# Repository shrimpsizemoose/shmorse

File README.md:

# Morse Code ATtiny85

Поупражняться с attiny85, светодиодами и пищалкой. В целом можно делать что угодно, но вообще идея что это что-то типа азбуки морзе, а кнопка это переключатель между состояниями.

Схема сделана в KiCad, вот отличный туториал который я использовал чтобы разобраться, как это делается: https://www.youtube.com/watch?v=vLnu21fS22s&list=PLUOaI24LpvQPls1Ru_qECJrENwzD7XImd

## Schematic

Собственно, схема. Никаких выключателей, только хардкор, только писк

## PCB Layout

Всё залито землёй, поэтому ножки которые идут на землю никуда не идут, _удобно!_

## Build Examples

Один из резисторов стоит неудобно, но в целом выкрутиться можно если не присоединять слот под батарейку.

## Компоненты
* Микроконтроллер ATtiny85-20P (ATtiny45 тоже подойдёт)
* 8-pin панелька под микросхему (можно без неё если не планируешь вынимать микроконтроллер)
* 3x 1kΩ резистора
* 3x 5mm светодиодов
* 1x 6x6mm кнопка
* 1x пищалка 12mm (растояние между ножек 7.5мм)
* 1x разъём под батарейку CR2032 -- :warning: в v1.0 нестандартное расстояние между ножек 20.5mm, возможно проще без него проводки к контактам припаять

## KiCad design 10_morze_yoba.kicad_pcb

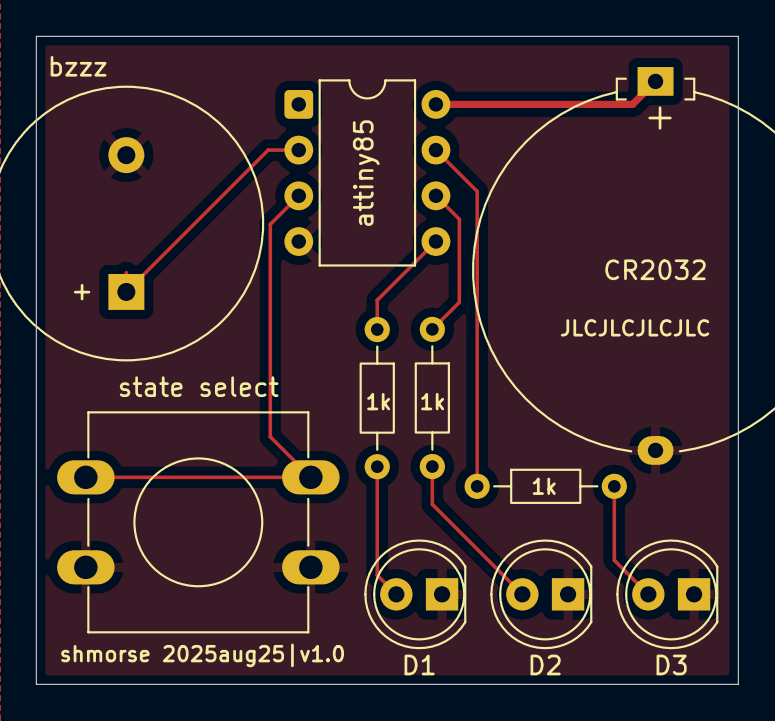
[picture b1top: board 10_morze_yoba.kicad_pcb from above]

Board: 4 copper layers, 39.0 x 36.0 mm, 10 parts (0 on the bottom side), 10 nets.

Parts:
CR2032: Battery_Cell; Battery_Panasonic_CR2032-HFN_Horizontal_CircularHoles
D1, D2, D3: LED; LED_D5.0mm
R1, R2, R3: 1k; R_Axial_DIN0204_L3.6mm_D1.6mm_P7.62mm_Horizontal
attiny85: ATtiny85-20P; DIP-8_W7.62mm
bzzz: Buzzer; Buzzer_15x7.5RM7.6
state select: SW_Push; SW_PUSH-12mm

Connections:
GND: CR2032.2 (-), D1.1 (K), D2.1 (K), D3.1 (K), attiny85.4 (GND), bzzz.2 (-), state select.1
unnamed: attiny85.2 (XTAL1/PB3), bzzz.1 (+)
unnamed: D1.2 (A), R1.2
unnamed: D2.2 (A), R2.2
unnamed: D3.2 (A), R3.2
unnamed: R1.1, attiny85.5 (AREF/PB0)
unnamed: R2.1, attiny85.6 (PB1)
unnamed: R3.1, attiny85.7 (PB2)
unnamed: attiny85.3 (XTAL2/PB4), state select.2
VCC: CR2032.1 (+), attiny85.8 (VCC)

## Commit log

2025-09-21 commit v1.0 files
